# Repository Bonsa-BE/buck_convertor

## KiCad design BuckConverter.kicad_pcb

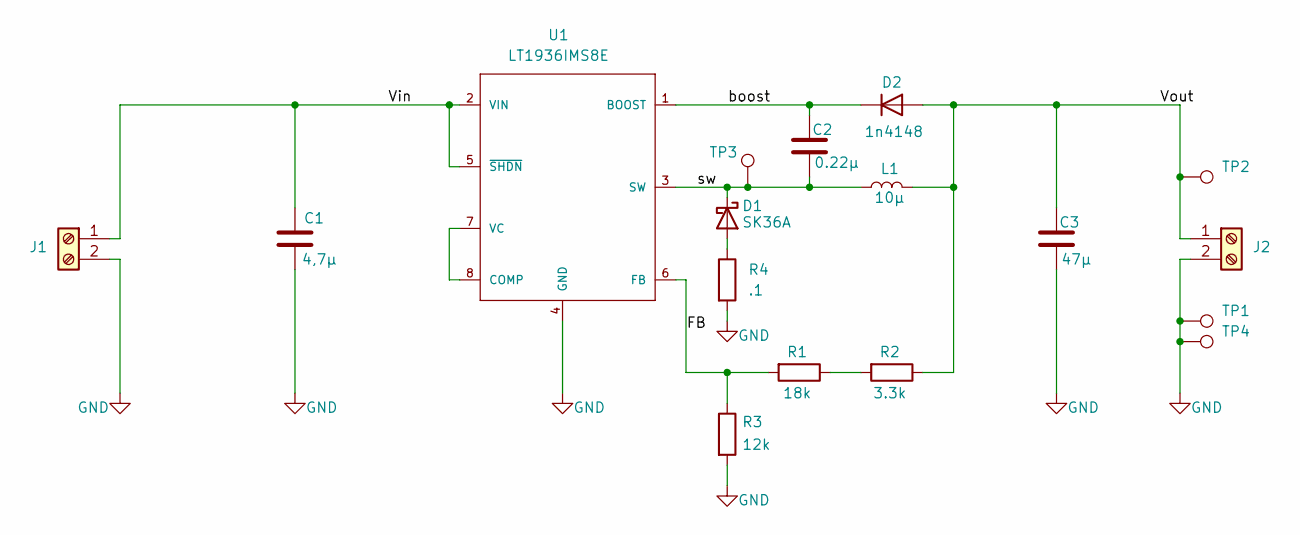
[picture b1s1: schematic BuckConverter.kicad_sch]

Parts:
C1: 4,7µ; C_0805_2012Metric_Pad1.18x1.45mm_HandSolder
C2: 0.22µ; C_0805_2012Metric_Pad1.18x1.45mm_HandSolder
C3: 47µ; C_1210_3225Metric_Pad1.33x2.70mm_HandSolder
D1: SK36A; D_SMA_Handsoldering
D2: 1n4148; D_SOD-323_HandSoldering
J1, J2: Screw_Terminal_01x02; TerminalBlock_Xinya_XY308-2.54-2P_1x02_P2.54mm_Horizontal
L1: 10µ; L_Wurth_WE-LQSH-2512
R1: 18k; R_0805_2012Metric_Pad1.20x1.40mm_HandSolder
R2: 3.3k; R_0805_2012Metric_Pad1.20x1.40mm_HandSolder
R3: 12k; R_0805_2012Metric_Pad1.20x1.40mm_HandSolder
R4: .1; R_0805_2012Metric_Pad1.20x1.40mm_HandSolder
TP1, TP2, TP3, TP4: TestPoint; TestPoint_Loop_D2.54mm_Drill1.5mm_Beaded
U1: LT1936IMS8E; MSOP-8-1EP_3x3mm_P0.65mm_EP1.73x1.85mm_ThermalVias; MANUFACTURER_PART_NUMBER lt1936ims8e

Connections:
/FB: R1.2, R3.1, U1.6 (FB)
/Vin: C1.1, J1.1, U1.2 (VIN), U1.5 (~SHDN)
/Vout: C3.1, D2.2 (A), J2.1, L1.2, R2.1, TP2.1 (1_1)
/boost: C2.1, D2.1 (K), U1.1 (BOOST)
/sw: C2.2, D1.1 (K), L1.1, TP3.1 (1_1), U1.3 (SW)
GND: C1.2, C3.2, J1.2, J2.2, R3.2, R4.2, TP1.1 (1_1), TP4.1 (1_1), U1.4 (GND)
unnamed: D1.2 (A), R4.1
unnamed: R1.1, R2.2
unnamed: U1.7 (VC), U1.8 (COMP)

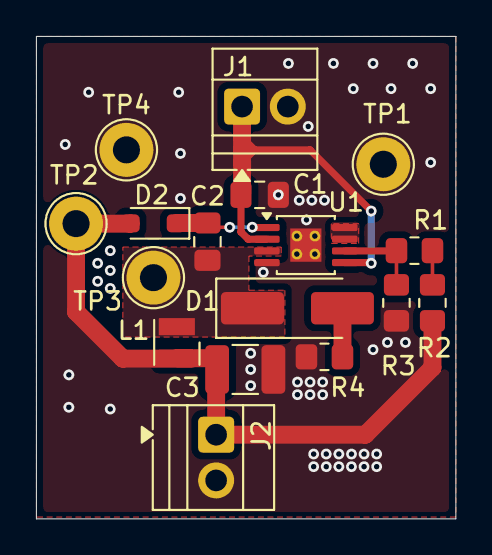
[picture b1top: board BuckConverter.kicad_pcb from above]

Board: 2 copper layers, 23.3 x 26.8 mm, 17 parts (0 on the bottom side), 9 nets.
